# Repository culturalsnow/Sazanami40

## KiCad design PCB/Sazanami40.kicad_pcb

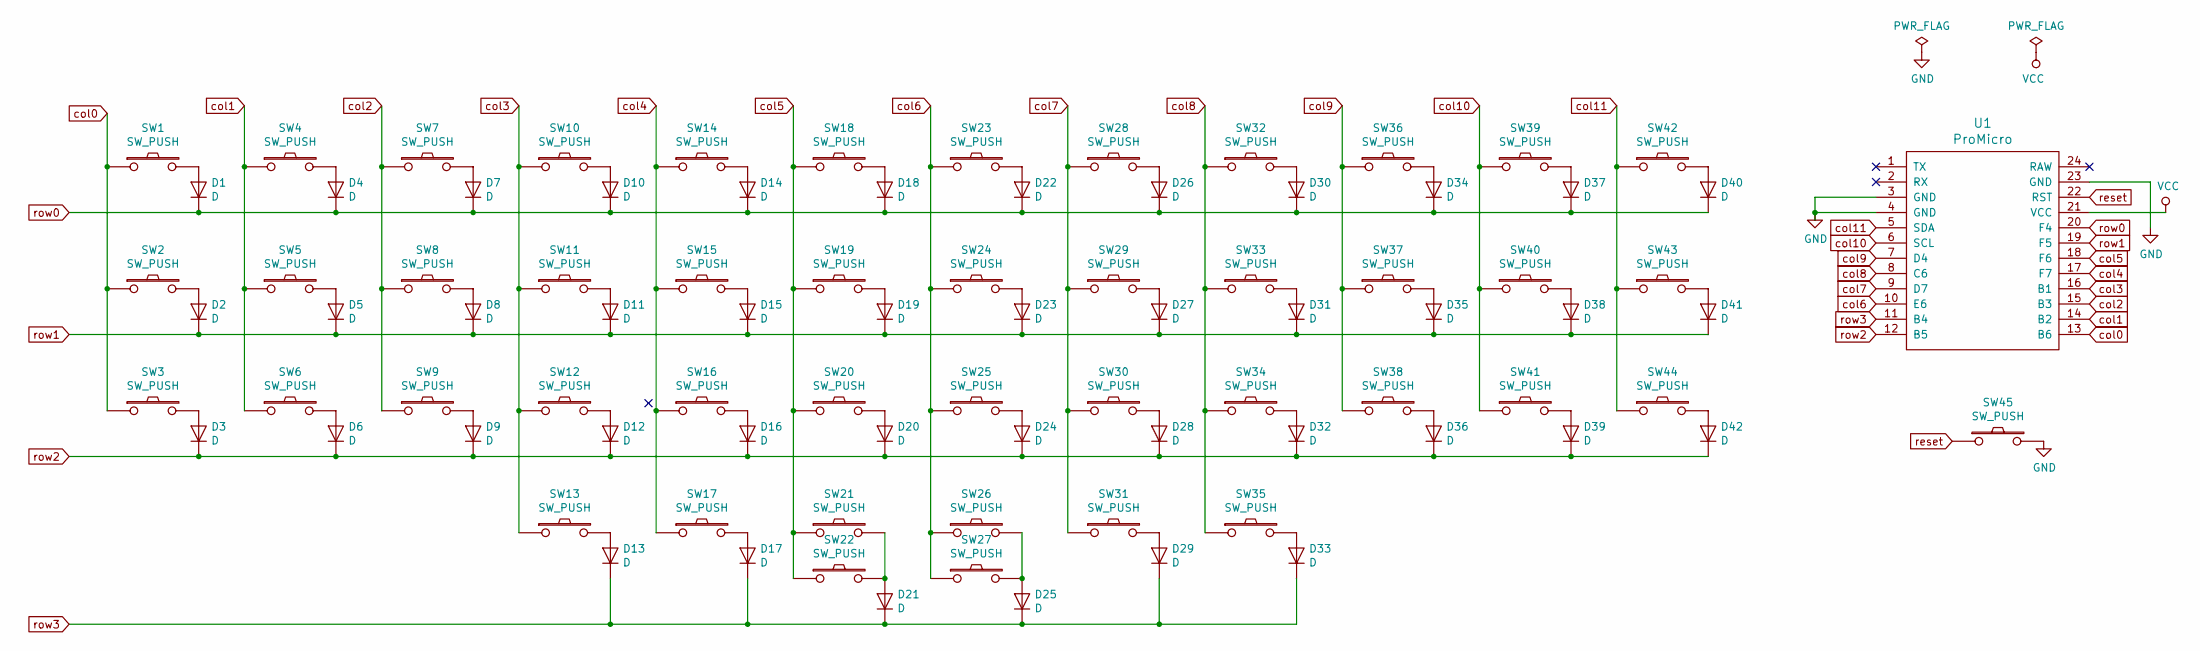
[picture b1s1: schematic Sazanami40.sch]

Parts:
D1, D2, D3, D4, D5, D6, D7, D8, D9, D10, D11, D12, D13, D14, D15, D16, D17, D18, D19, D20, D21, D22, D23, D24, D25, D26, D27, D28, D29, D30, D31, D32, D33, D34, D35, D36, D37, D38, D39, D40, D41, D42: D; D_SOD-123
SW1, SW2, SW3, SW4, SW5, SW6, SW7, SW8, SW9, SW10, SW11, SW12, SW13, SW14, SW15, SW16, SW17, SW18, SW19, SW20, SW21, SW22, SW23, SW24, SW25, SW26, SW27, SW28, SW29, SW30, SW31, SW32, SW33, SW34, SW35, SW36, SW37, SW38, SW39, SW40, SW41, SW42, SW43, SW44: SW_PUSH; MX_PCB_100H
SW45: SW_PUSH; ResetSW
U1: ProMicro; ProMicro_v2_Backside

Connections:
GND: SW45.2, U1.3 (GND), U1.4 (GND), U1.23 (GND)
unnamed: D1.2 (A), SW1.2
unnamed: D2.2 (A), SW2.2
unnamed: D3.2 (A), SW3.2
unnamed: D4.2 (A), SW4.2
unnamed: D5.2 (A), SW5.2
unnamed: D6.2 (A), SW6.2
unnamed: D7.2 (A), SW7.2
unnamed: D8.2 (A), SW8.2
unnamed: D9.2 (A), SW9.2
unnamed: D10.2 (A), SW10.2
unnamed: D11.2 (A), SW11.2
unnamed: D12.2 (A), SW12.2
unnamed: D13.2 (A), SW13.2
unnamed: D14.2 (A), SW14.2
unnamed: D15.2 (A), SW15.2
unnamed: D16.2 (A), SW16.2
unnamed: D17.2 (A), SW17.2
unnamed: D18.2 (A), SW18.2
unnamed: D19.2 (A), SW19.2
unnamed: D20.2 (A), SW20.2
unnamed: D21.2 (A), SW21.2, SW22.2
unnamed: D22.2 (A), SW23.2
unnamed: D23.2 (A), SW24.2
unnamed: D24.2 (A), SW25.2
unnamed: D25.2 (A), SW26.2, SW27.2
unnamed: D26.2 (A), SW28.2
unnamed: D27.2 (A), SW29.2
unnamed: D28.2 (A), SW30.2
unnamed: D29.2 (A), SW31.2
unnamed: D30.2 (A), SW32.2
unnamed: D31.2 (A), SW33.2
unnamed: D32.2 (A), SW34.2
unnamed: D33.2 (A), SW35.2
unnamed: D34.2 (A), SW36.2
unnamed: D35.2 (A), SW37.2
unnamed: D36.2 (A), SW38.2
unnamed: D37.2 (A), SW39.2
unnamed: D38.2 (A), SW40.2
unnamed: D39.2 (A), SW41.2
unnamed: D40.2 (A), SW42.2
unnamed: D41.2 (A), SW43.2
unnamed: D42.2 (A), SW44.2
VCC: U1.21 (VCC)
col0: SW1.1, SW2.1, SW3.1, U1.13 (B6)
col1: SW4.1, SW5.1, SW6.1, U1.14 (B2)
col2: SW7.1, SW8.1, SW9.1, U1.15 (B3)
col3: SW10.1, SW11.1, SW12.1, SW13.1, U1.16 (B1)
col4: SW14.1, SW15.1, SW16.1, SW17.1, U1.17 (F7)
col5: SW18.1, SW19.1, SW20.1, SW21.1, SW22.1, U1.18 (F6)
col6: SW23.1, SW24.1, SW25.1, SW26.1, SW27.1, U1.10 (E6)
col7: SW28.1, SW29.1, SW30.1, SW31.1, U1.9 (D7)
col8: SW32.1, SW33.1, SW34.1, SW35.1, U1.8 (C6)
col9: SW36.1, SW37.1, SW38.1, U1.7 (D4)
col10: SW39.1, SW40.1, SW41.1, U1.6 (SCL)
col11: SW42.1, SW43.1, SW44.1, U1.5 (SDA)
reset: SW45.1, U1.22 (RST)
row0: D1.1 (K), D4.1 (K), D7.1 (K), D10.1 (K), D14.1 (K), D18.1 (K), D22.1 (K), D26.1 (K), D30.1 (K), D34.1 (K), D37.1 (K), D40.1 (K), U1.20 (F4)
row1: D2.1 (K), D5.1 (K), D8.1 (K), D11.1 (K), D15.1 (K), D19.1 (K), D23.1 (K), D27.1 (K), D31.1 (K), D35.1 (K), D38.1 (K), D41.1 (K), U1.19 (F5)
row2: D3.1 (K), D6.1 (K), D9.1 (K), D12.1 (K), D16.1 (K), D20.1 (K), D24.1 (K), D28.1 (K), D32.1 (K), D36.1 (K), D39.1 (K), D42.1 (K), U1.12 (B5)
row3: D13.1 (K), D17.1 (K), D21.1 (K), D25.1 (K), D29.1 (K), D33.1 (K), U1.11 (B4)

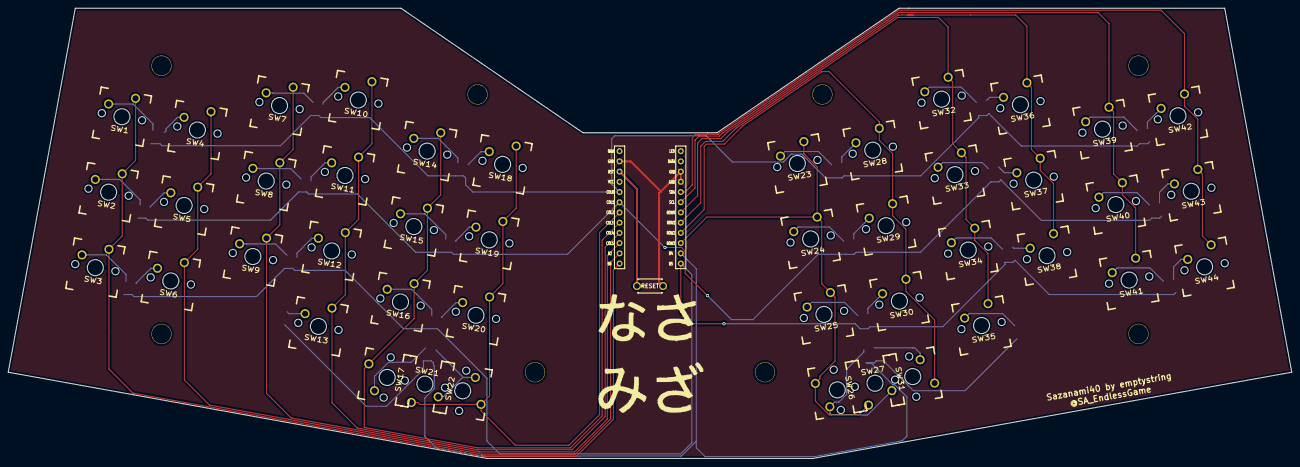
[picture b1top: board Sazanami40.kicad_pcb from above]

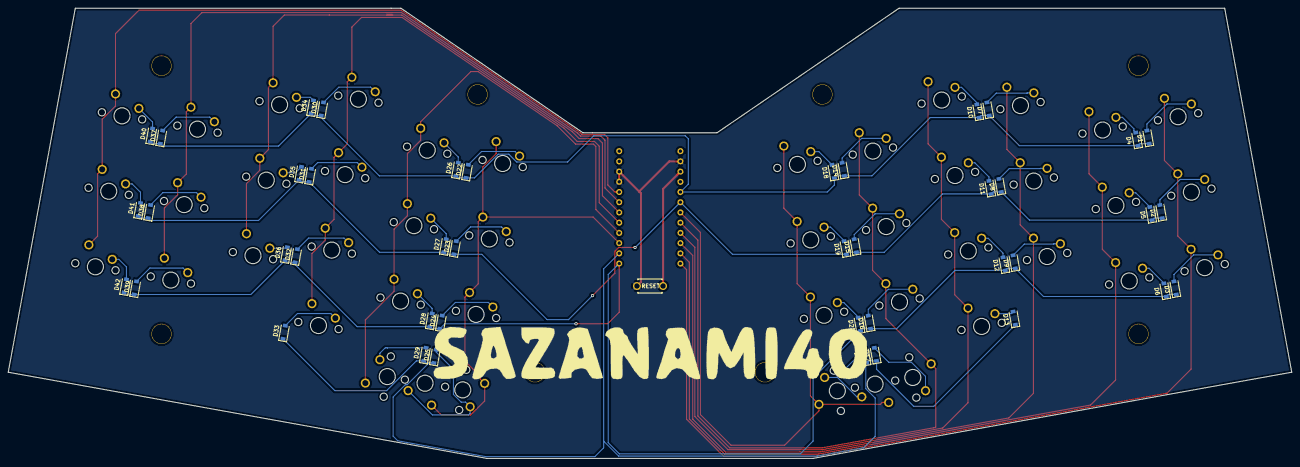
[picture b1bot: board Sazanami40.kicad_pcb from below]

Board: 2 copper layers, 319.1 x 111.9 mm, 96 parts (42 on the bottom side), 60 nets.

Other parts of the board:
Ref**: Val**; HOLE
Ref**#2, Ref**#3, Ref**#4, Ref**#5, Ref**#6, Ref**#7, Ref**#8: Val**; HOLE

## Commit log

2019-04-03 pcb schematic
2019-04-03 pcb switch positions added
2019-04-03 layout complete :
2019-04-04 first draft PCB complete
2019-04-04 pcb complete
2019-04-05 fixed reset switch position
2019-04-06 dxf files added
2019-04-06 switch openings
2019-04-06 removed autosave
2019-04-07 new logo front
